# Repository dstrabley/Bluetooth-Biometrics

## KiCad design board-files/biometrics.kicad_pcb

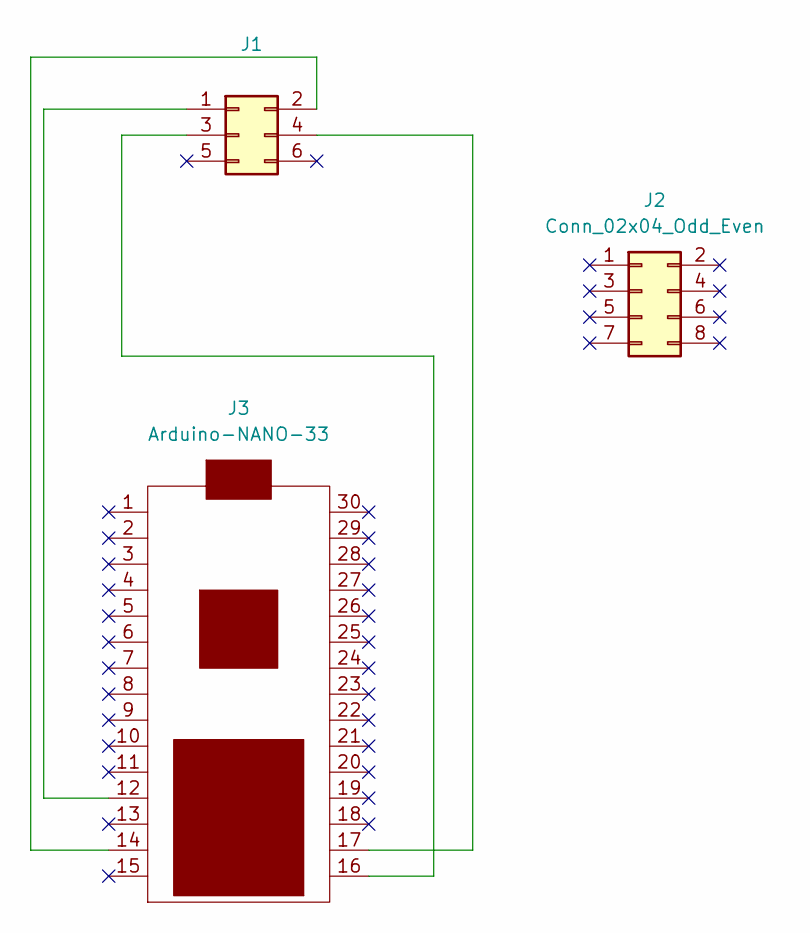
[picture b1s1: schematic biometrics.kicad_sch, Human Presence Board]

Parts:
J1: Conn_02x03_Odd_Even; PinSocket_2x03_P2.00mm_Vertical
J2: Conn_02x04_Odd_Even; PinSocket_2x04_P2.00mm_Vertical
J3: Arduino-NANO-33; NANO_33_Footprint_SMD_Castell

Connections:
unnamed: J1.1, J3.12
unnamed: J1.2, J3.14
unnamed: J1.3, J3.16
unnamed: J1.4, J3.17

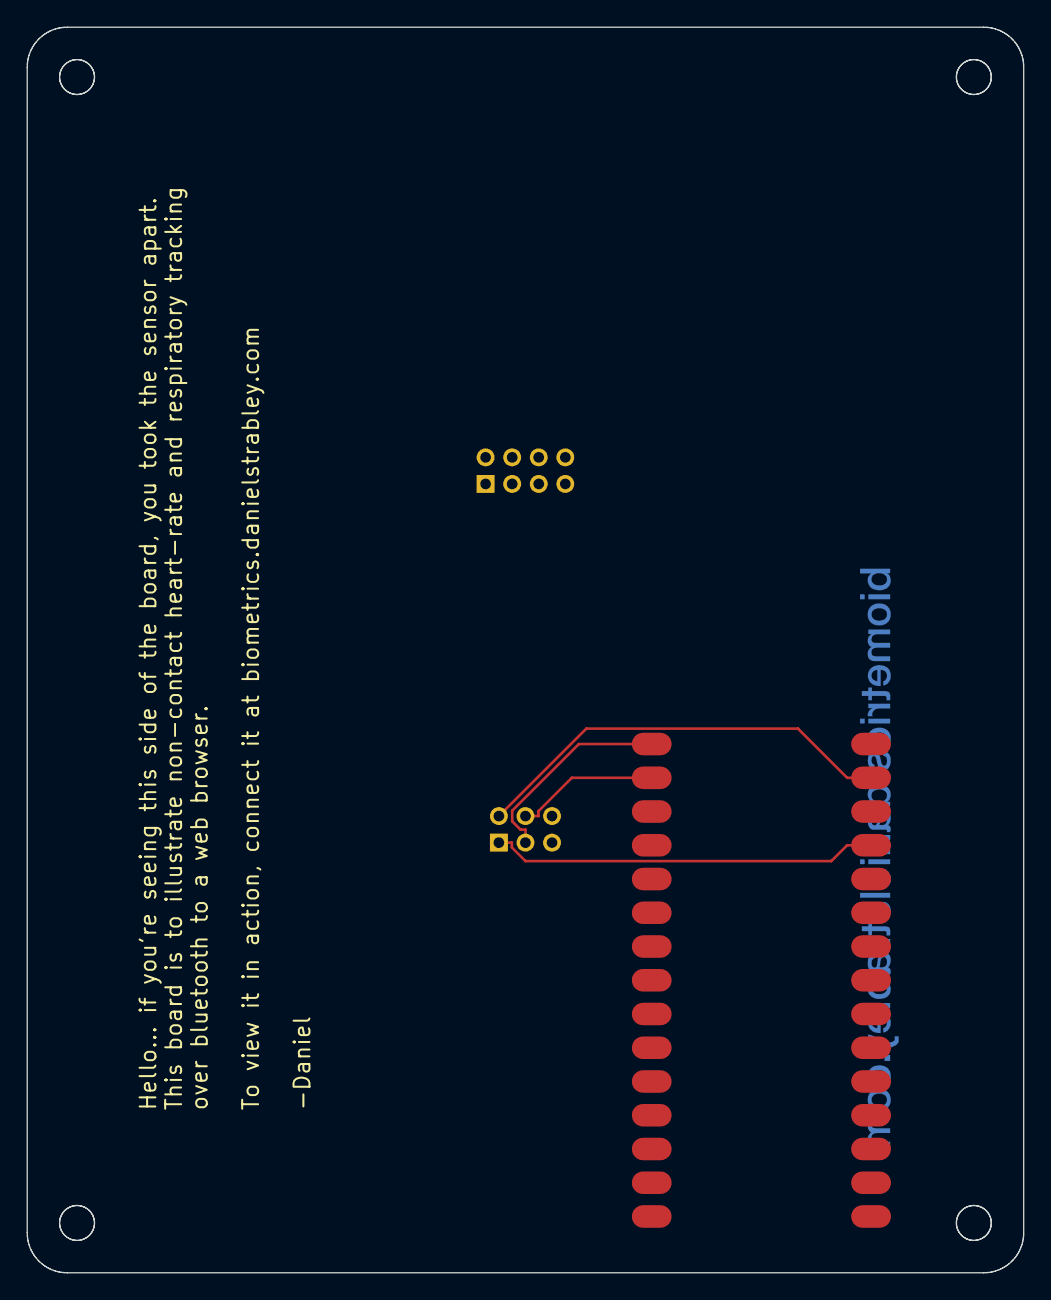
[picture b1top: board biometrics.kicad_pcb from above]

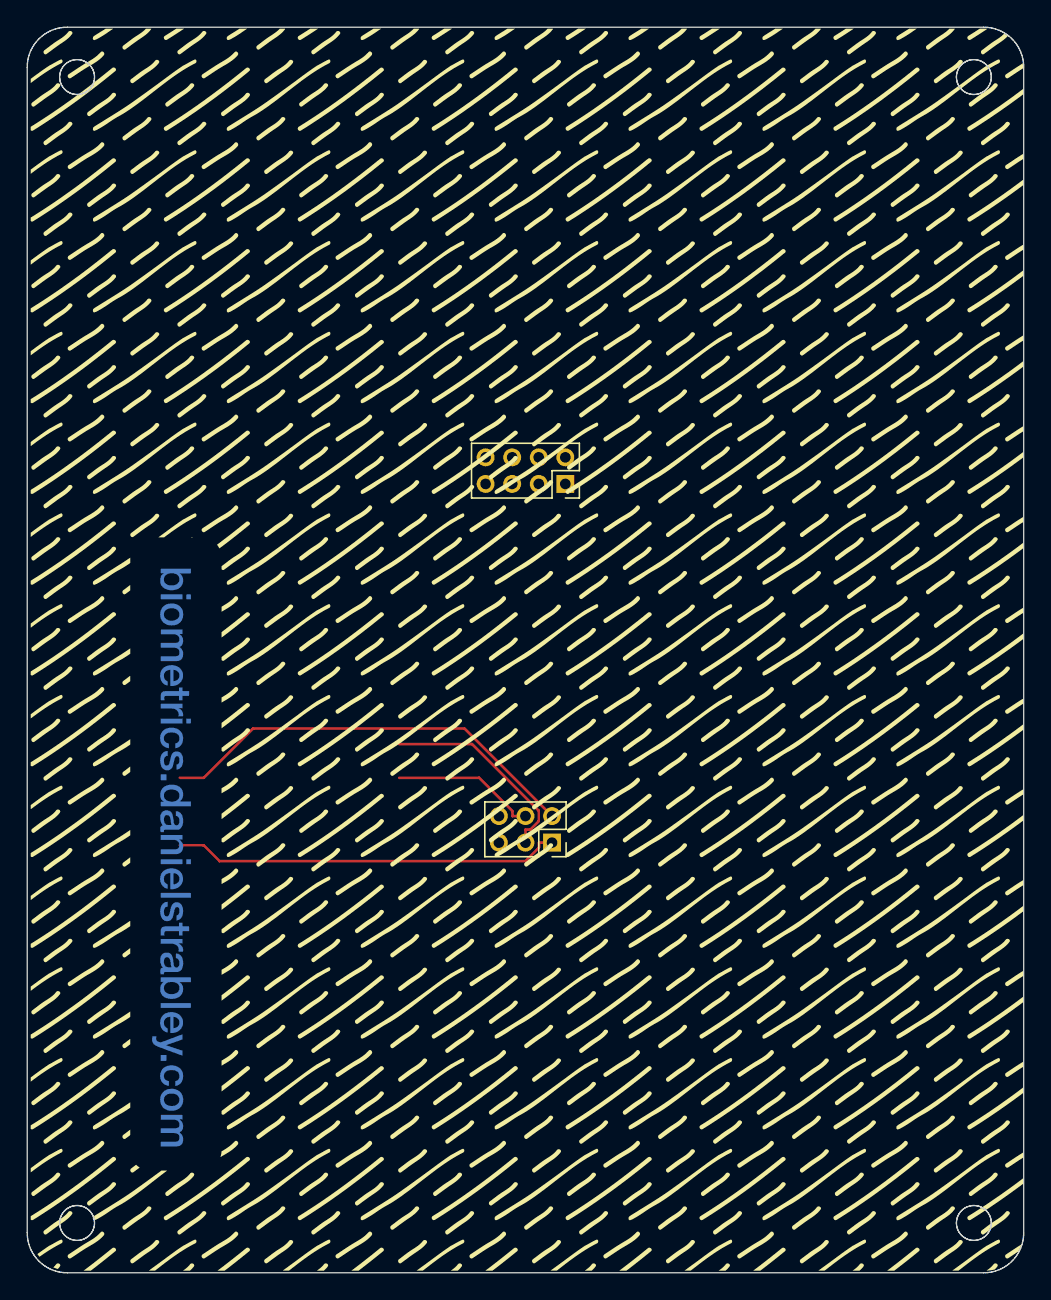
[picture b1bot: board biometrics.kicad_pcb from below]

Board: 2 copper layers, 75.0 x 93.7 mm, 3 parts (2 on the bottom side), 4 nets.

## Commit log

2023-07-18 Adding biometrics to the repo
2023-07-19 updating SVGS
2023-07-22 modified svgs and updating to working code
2023-07-22 Adding breath rate and styling the page
2023-07-22 Added distance and restyled the html
2023-07-22 Removing Index Label
2023-07-22 Adding console log messaging
2023-07-23 minor changes
2023-07-23 boop
2023-07-23 removing dead files
2023-07-23 removing mac bullshit
2023-07-23 cleanup
2023-07-23 Adding console log functionality
2023-07-23 Adding time function for console log
2023-07-23 updating output
2023-07-24 Making it work on movile... eveb tho its not supported.... the fuck am i doing?
2023-07-25 updating styleing
2023-07-25 Commenting out the line for serial connection so it will run off batteries
2023-07-26 Adding function to sewap UUIDs on the client side for some stupid ass reason
2023-07-26 formatting clean up
